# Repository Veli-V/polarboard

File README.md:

# polarboard

WIP: not ready for use
Hobby project, test of making own, portable, ergonomic keyboard.

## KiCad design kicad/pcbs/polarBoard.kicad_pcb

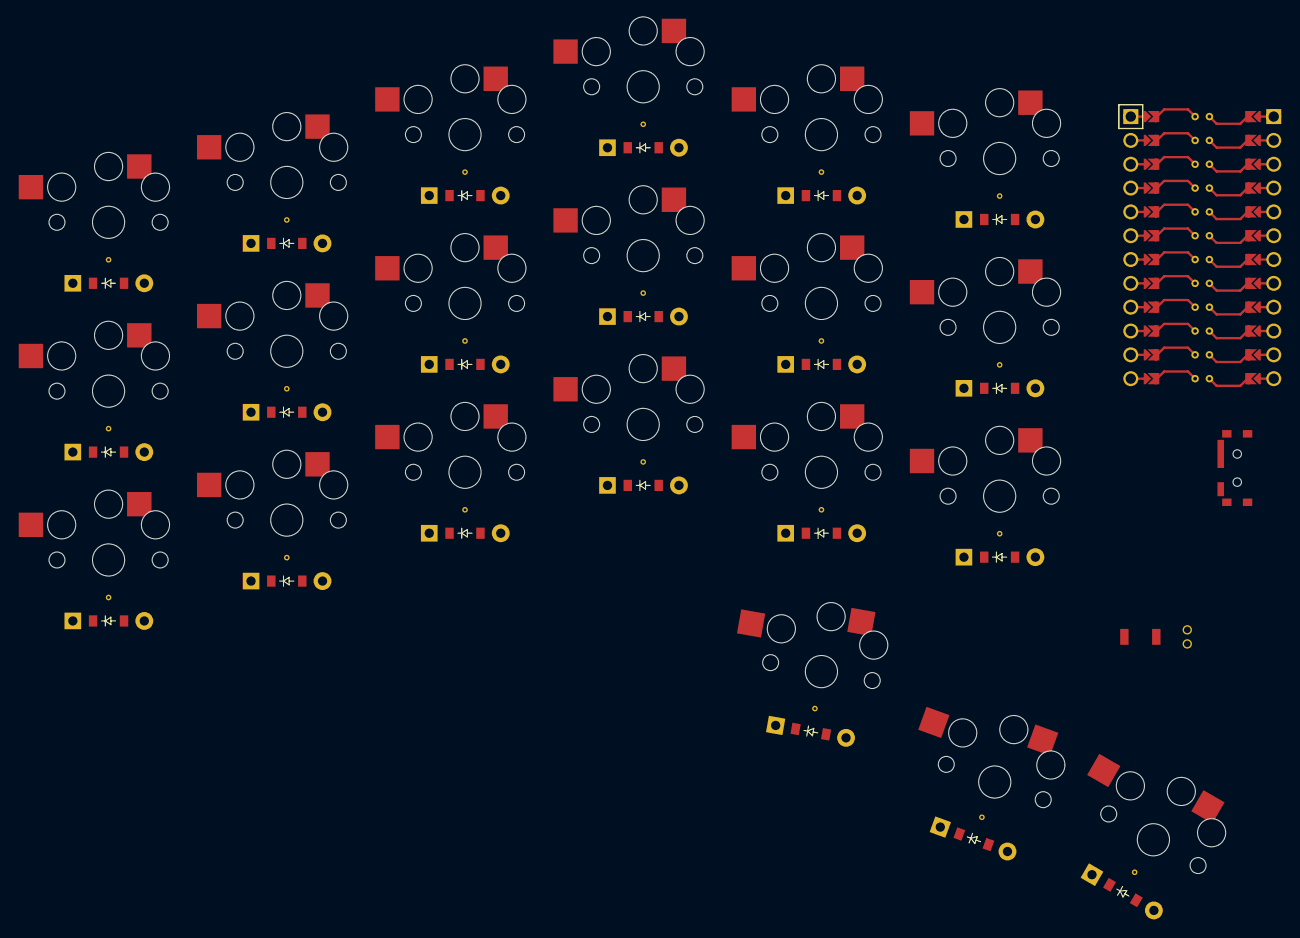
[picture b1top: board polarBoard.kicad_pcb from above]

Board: 2 copper layers, 43 parts (0 on the bottom side), 32 nets, no tracks yet.

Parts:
D1, D2, D3, D4, D5, D6, D7, D8, D9, D10, D11, D12, D13, D14, D15, D16, D17, D18, D19, D20, D21: ComboDiode
MCU1: ProMicro
S1, S2, S3, S4, S5, S6, S7, S8, S9, S10, S11, S12, S13, S14, S15, S16, S17, S18, S19, S20, S21: PG1350

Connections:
GND: MCU1.2, MCU1.21, MCU1.22
P3: D3.1, D3.2, D6.1, D6.2, D9.1, D9.2, D12.1, D12.2, D15.1, D15.2, D18.1, D18.2, MCU1.19
P4: D2.1, D2.2, D5.1, D5.2, D8.1, D8.2, D11.1, D11.2, D14.1, D14.2, D17.1, D17.2, MCU1.18
P5: D1.1, D1.2, D4.1, D4.2, D7.1, D7.2, D10.1, D10.2, D13.1, D13.2, D16.1, D16.2, MCU1.17
P6: D19.1, D19.2, D20.1, D20.2, D21.1, D21.2, MCU1.16
P14: MCU1.10, S16.2, S17.2, S18.2, S21.2
P15: MCU1.9, S13.2, S14.2, S15.2, S20.2
P18: MCU1.8, S10.2, S11.2, S12.2, S19.2
P19: MCU1.7, S7.2, S8.2, S9.2
P20: MCU1.6, S4.2, S5.2, S6.2
P21: MCU1.5, S1.2, S2.2, S3.2
index_bottom: D13.1, D13.2, S13.1
index_home: D14.1, D14.2, S14.1
index_top: D15.1, D15.2, S15.1
inner_bottom: D16.1, D16.2, S16.1
inner_default: D19.1, D19.2, S19.1
inner_home: D17.1, D17.2, S17.1
inner_top: D18.1, D18.2, S18.1
middle_bottom: D10.1, D10.2, S10.1
middle_home: D11.1, D11.2, S11.1
middle_top: D12.1, D12.2, S12.1
pinky_bottom: D4.1, D4.2, S4.1
pinky_home: D5.1, D5.2, S5.1
pinky_top: D6.1, D6.2, S6.1
pinkyreach_bottom: D1.1, D1.2, S1.1
pinkyreach_home: D2.1, D2.2, S2.1
pinkyreach_top: D3.1, D3.2, S3.1
reachy_default: D21.1, D21.2, S21.1
ring_bottom: D7.1, D7.2, S7.1
ring_home: D8.1, D8.2, S8.1
ring_top: D9.1, D9.2, S9.1
tucky_default: D20.1, D20.2, S20.1

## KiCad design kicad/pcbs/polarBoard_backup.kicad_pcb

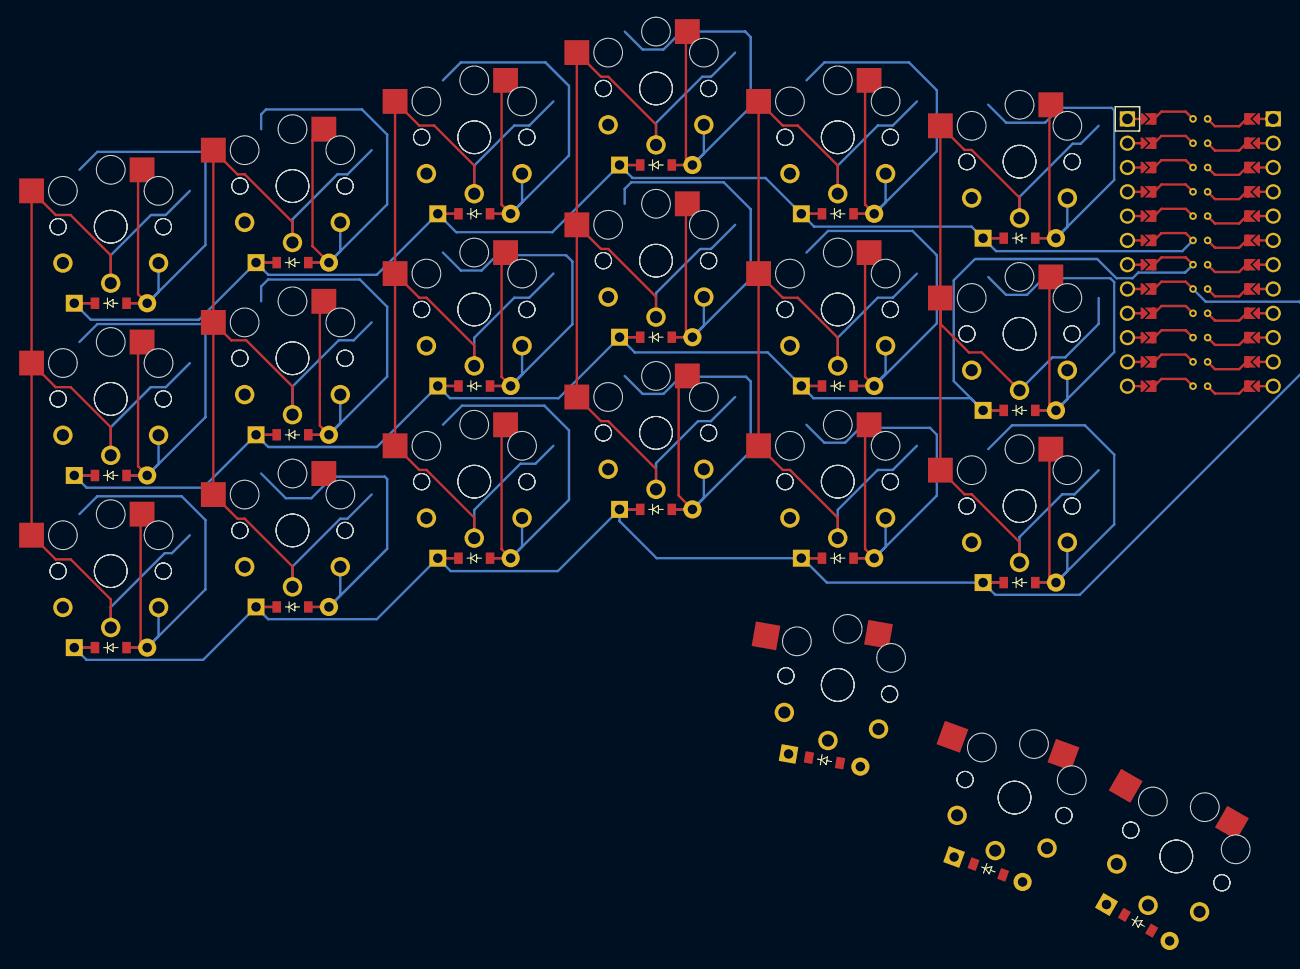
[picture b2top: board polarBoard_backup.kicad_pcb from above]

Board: 2 copper layers, 64 parts (0 on the bottom side), 32 nets.

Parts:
D1, D2, D3, D4, D5, D6, D7, D8, D9, D10, D11, D12, D13, D14, D15, D16, D17, D18, D19, D20, D21: ComboDiode
MCU1: ProMicro
S1, S2, S3, S4, S5, S6, S7, S8, S9, S10, S11, S12, S13, S14, S15, S16, S17, S18, S19, S20, S21, S22, S23, S24, S25, S26, S27, S28, S29, S30, S31, S32, S33, S34, S35, S36, S37, S38, S39, S40, S41, S42: PG1350

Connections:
GND: MCU1.2, MCU1.21, MCU1.22
P3: D3.1, D3.2, D6.1, D6.2, D9.1, D9.2, D12.1, D12.2, D15.1, D15.2, D18.1, D18.2, MCU1.19
P4: D2.1, D2.2, D5.1, D5.2, D8.1, D8.2, D11.1, D11.2, D14.1, D14.2, D17.1, D17.2, MCU1.18
P5: D1.1, D1.2, D4.1, D4.2, D7.1, D7.2, D10.1, D10.2, D13.1, D13.2, D16.1, D16.2, MCU1.17
P6: D19.1, D19.2, D20.1, D20.2, D21.1, D21.2, MCU1.16
P14: MCU1.10, S31.2, S32.2, S33.2, S34.2, S35.2, S36.2, S41.2, S42.2
P15: MCU1.9, S25.2, S26.2, S27.2, S28.2, S29.2, S30.2, S39.2, S40.2
P18: MCU1.8, S19.2, S20.2, S21.2, S22.2, S23.2, S24.2, S37.2, S38.2
P19: MCU1.7, S13.2, S14.2, S15.2, S16.2, S17.2, S18.2
P20: MCU1.6, S7.2, S8.2, S9.2, S10.2, S11.2, S12.2
P21: MCU1.5, S1.2, S2.2, S3.2, S4.2, S5.2, S6.2
index_bottom: D13.1, D13.2, S25.1, S26.1
index_home: D14.1, D14.2, S27.1, S28.1
index_top: D15.1, D15.2, S29.1, S30.1
inner_bottom: D16.1, D16.2, S31.1, S32.1
inner_default: D19.1, D19.2, S37.1, S38.1
inner_home: D17.1, D17.2, S33.1, S34.1
inner_top: D18.1, D18.2, S35.1, S36.1
middle_bottom: D10.1, D10.2, S19.1, S20.1
middle_home: D11.1, D11.2, S21.1, S22.1
middle_top: D12.1, D12.2, S23.1, S24.1
pinky_bottom: D4.1, D4.2, S7.1, S8.1
pinky_home: D5.1, D5.2, S9.1, S10.1
pinky_top: D6.1, D6.2, S11.1, S12.1
pinkyreach_bottom: D1.1, D1.2, S1.1, S2.1
pinkyreach_home: D2.1, D2.2, S3.1, S4.1
pinkyreach_top: D3.1, D3.2, S5.1, S6.1
reachy_default: D21.1, D21.2, S41.1, S42.1
ring_bottom: D7.1, D7.2, S13.1, S14.1
ring_home: D8.1, D8.2, S15.1, S16.1
ring_top: D9.1, D9.2, S17.1, S18.1
tucky_default: D20.1, D20.2, S39.1, S40.1

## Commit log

2022-12-06 Initial
2022-12-08 Wip, keys in place
